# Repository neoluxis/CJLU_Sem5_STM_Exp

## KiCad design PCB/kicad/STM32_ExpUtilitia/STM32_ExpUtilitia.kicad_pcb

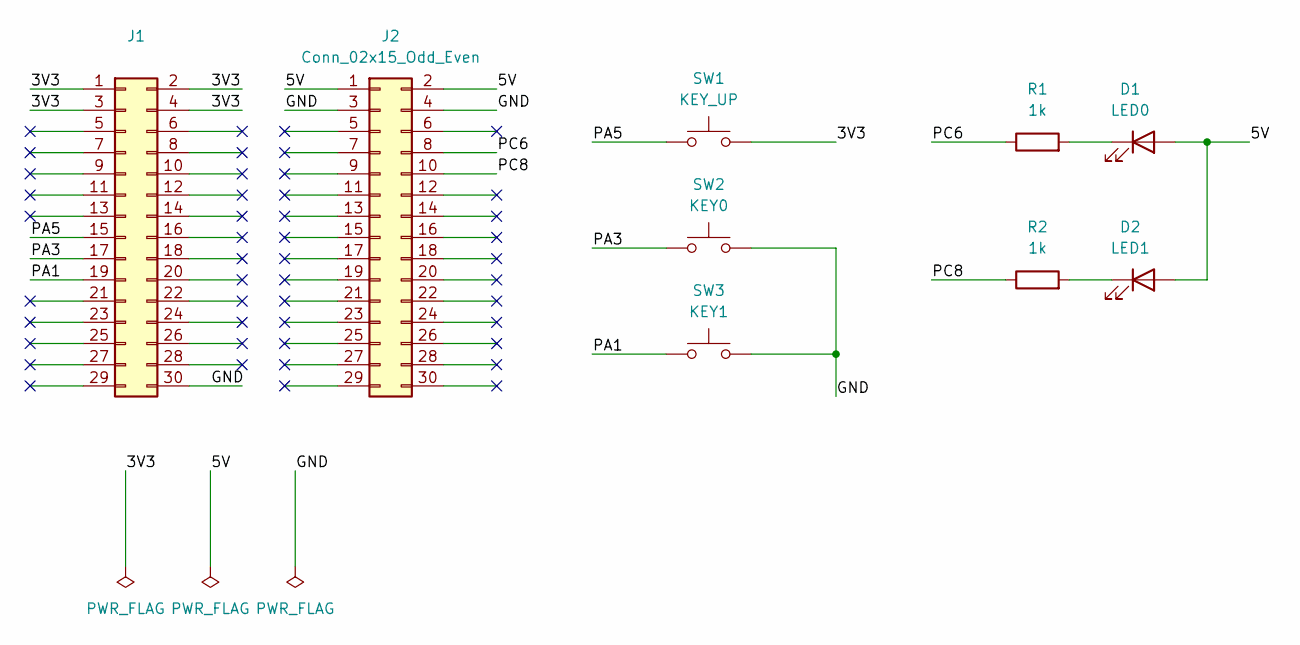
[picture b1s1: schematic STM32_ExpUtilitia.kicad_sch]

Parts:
D1: LED0; LED_D5.0mm
D2: LED1; LED_D5.0mm
J1, J2: Conn_02x15_Odd_Even; PinHeader_2x15_P2.54mm_Vertical
R1, R2: 1k; R_Axial_DIN0204_L3.6mm_D1.6mm_P5.08mm_Horizontal
SW1: KEY_UP; SW_PUSH_6mm
SW2: KEY0; SW_PUSH_6mm
SW3: KEY1; SW_PUSH_6mm

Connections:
/3V3: J1.1, J1.2, J1.3, J1.4, SW1.2
/5V: D1.2 (A), D2.2 (A), J2.1, J2.2
/GND: J1.30, J2.3, J2.4, SW2.2, SW3.2
/PA1: J1.19, SW3.1
/PA3: J1.17, SW2.1
/PA5: J1.15, SW1.1
/PC6: J2.8, R1.1
/PC8: J2.10, R2.1
unnamed: D1.1 (K), R1.2
unnamed: D2.1 (K), R2.2

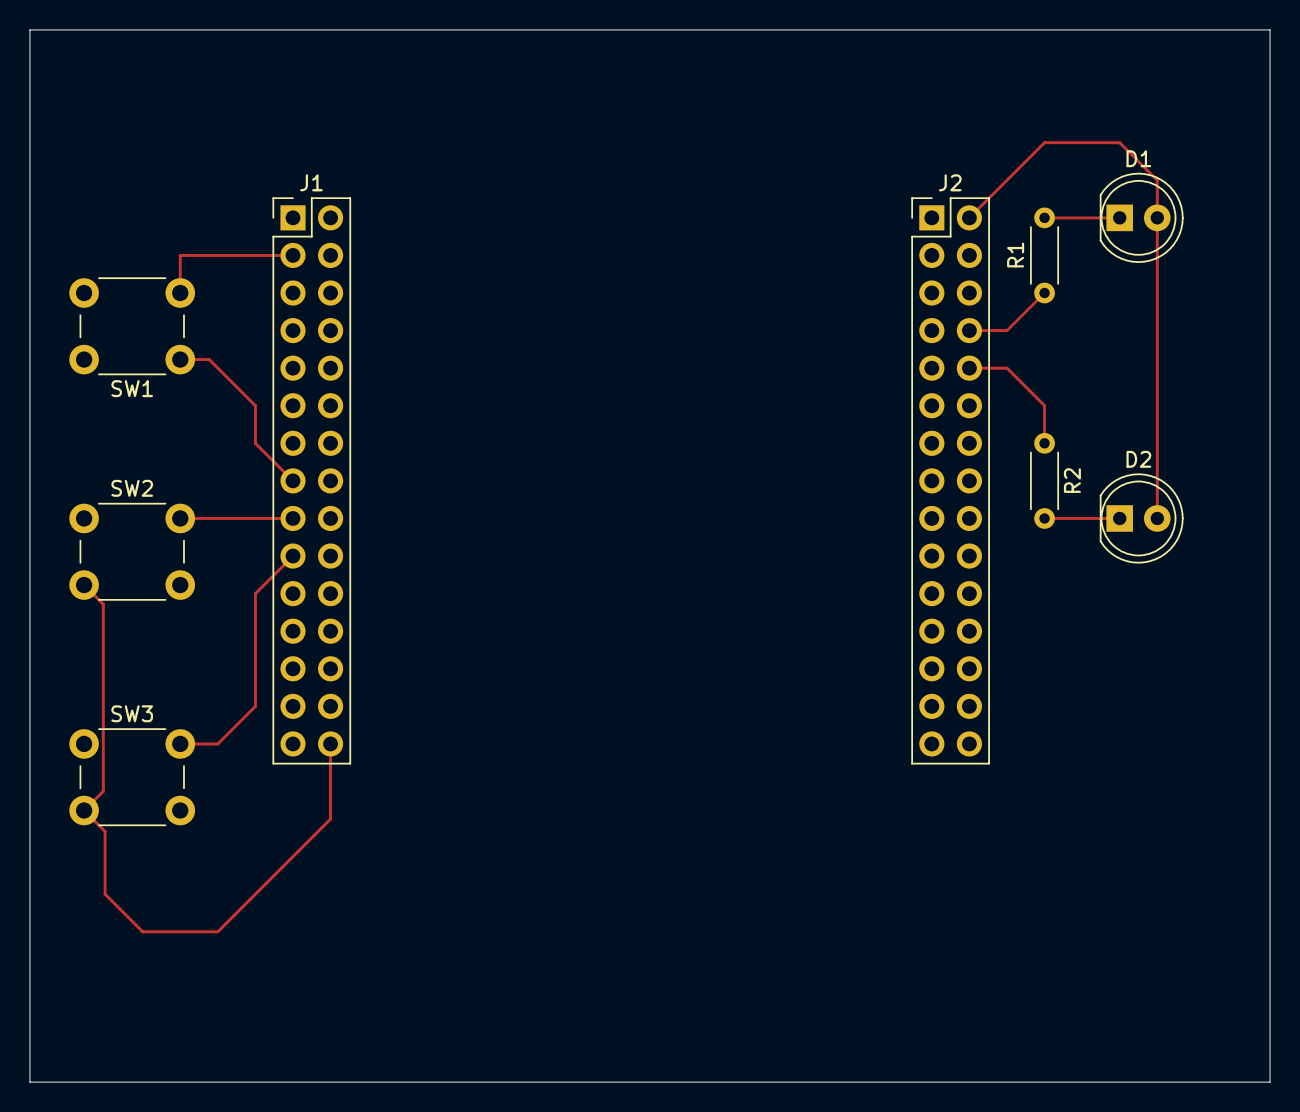
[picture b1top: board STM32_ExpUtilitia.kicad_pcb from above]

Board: 2 copper layers, 83.8 x 71.1 mm, 9 parts (0 on the bottom side), 10 nets.

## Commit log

2024-11-28 init exp1
2024-12-02 update basic pcb
2024-12-03 update exp 1 and exp 3
2024-12-06 Finish all with STM32 F1. Plan to draw schematics
2024-12-06 update pcb schema and layout
2024-12-07 la finn
2024-12-07 la finie
2024-12-07 upate finie, sum all
2025-01-13 add led pcb pack
